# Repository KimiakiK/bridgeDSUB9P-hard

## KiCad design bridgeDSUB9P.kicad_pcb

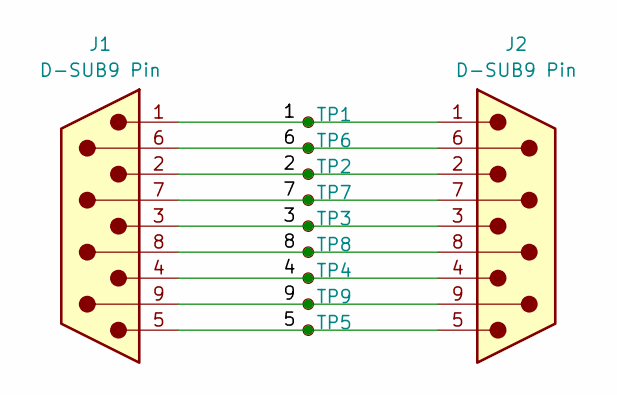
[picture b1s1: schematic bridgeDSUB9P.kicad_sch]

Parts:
J1, J2: D-SUB9 Pin; D-SUB9P
TP1, TP2, TP3, TP4, TP5, TP6, TP7, TP8, TP9: TestPoint; TestPoint_THTPad_D1.6mm_Drill1.0mm

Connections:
/1: J1.1, J2.1, TP1.1
/2: J1.2, J2.2, TP2.1
/3: J1.3, J2.3, TP3.1
/4: J1.4, J2.4, TP4.1
/5: J1.5, J2.5, TP5.1
/6: J1.6, J2.6, TP6.1
/7: J1.7, J2.7, TP7.1
/8: J1.8, J2.8, TP8.1
/9: J1.9, J2.9, TP9.1

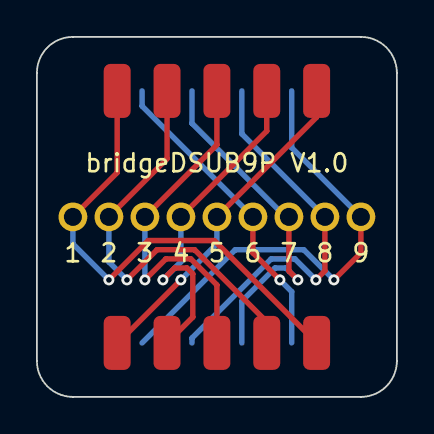
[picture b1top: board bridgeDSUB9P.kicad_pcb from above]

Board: 2 copper layers, 20.0 x 20.0 mm, 11 parts (0 on the bottom side), 9 nets.

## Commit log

2023-03-20 基板V1.0
